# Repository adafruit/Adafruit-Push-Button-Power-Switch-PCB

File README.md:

## Adafruit Push Button Power Switch PCB
<a href="http://www.adafruit.com/products/1400"><br/>
Click here to purchase one from the Adafruit shop</a>

The Adafruit Push-button Power Switch is a tidy little design that lets you control a DC power source using an everyday tactile button. The breakout uses a latching analog circuit that is triggered by a push of the button. Press once to turn on, then press again to turn off. The circuit uses a 3A P-FET to connect and disconnect the IN pin to the OUT pin. Works great from 3V to 14VDC and up to 3A (although the FET gets a little toasty at continuous 3A draw) yet has only 0.5uA quiescent current draw.

Using it is easy: connect the power source to Ground and IN, then the load from Ground to OUT. We include a 12mm tactile switch that works well but you can solder in your own switch as well. Press the button (or short the button pins) to alternate between on or off. A on-board red LED will light up when active so you know its working. There's a fourth KILL pin, which you can use to turn off the load and/or keep it off even if the button is pressed. When 1 or more volts is applied it will instantly turn off the FET. This allows your project to turn itself off.

Comes with a assembled & tested bread-board friendly breakout board with four mounting holes, a 12mm tactile button, and some 0.1" male header you can solder to the board to plug it into a breadboard.

PCB files for the Push Button Power Switch PCB. The format is EagleCAD schematic and board layout
- https://www.adafruit.com/products/1400

### License

Adafruit invests time and resources providing this open source design, please support Adafruit and open-source hardware by purchasing products from [Adafruit](https://www.adafruit.com)!

All text above must be included in any redistribution

Designed by Limor Fried/Ladyada for Adafruit Industries.
Creative Commons Attribution/Share-Alike, all text above must be included in any redistribution. 
See license.txt for additional information.

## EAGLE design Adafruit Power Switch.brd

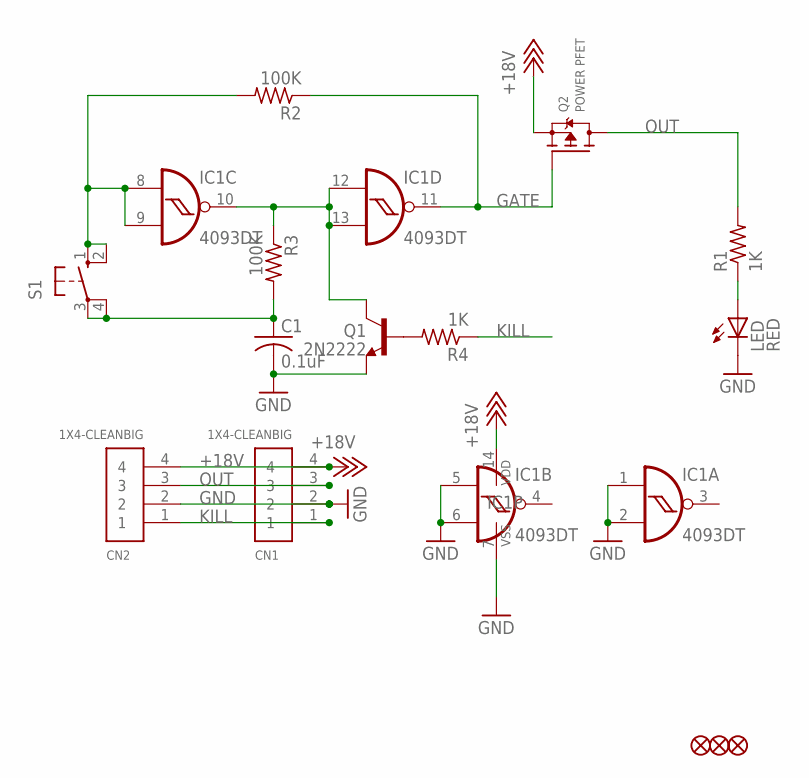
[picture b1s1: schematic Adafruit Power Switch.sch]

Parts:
C1: 0.1uF; C0805
CN1, CN2: 1X4-CLEANBIG; 1X04-CLEANBIG
FID1, FID2, FID3: FIDUCIAL""; FIDUCIAL_1MM
IC1: 4093DT; MC14093B-TSSOP14
LED: RED; CHIP-LED0805
Q1: 2N2222; SOT23-BEC
Q2: POWER PFET; SOT23-WIDE
R1, R4: 1K; R0805
R2, R3: 100K; R0805
S1: 40-XX-ROUND; B3F-40XX-ROUND

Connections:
+18V: CN1.4, CN2.4, IC1.14 (VDD), Q2.2 (S)
GATE: IC1.11 (O), Q2.1 (G), R2.1
GND: C1.2, CN1.2, CN2.2, IC1.1 (I0), IC1.2 (I1), IC1.5 (I0), IC1.6 (I1), IC1.7 (VSS), LED.C, Q1.E
KILL: CN1.1, CN2.1, R4.1
unnamed: Q1.B, R4.2
unnamed: IC1.10 (O), IC1.12 (I0), IC1.13 (I1), Q1.C, R3.1
unnamed: LED.A, R1.1
unnamed: C1.1, R3.2, S1.3, S1.4 (P1)
unnamed: IC1.8 (I0), IC1.9 (I1), R2.2, S1.1 (S), S1.2 (S1)
OUT: CN1.3, CN2.3, Q2.3 (D), R1.2

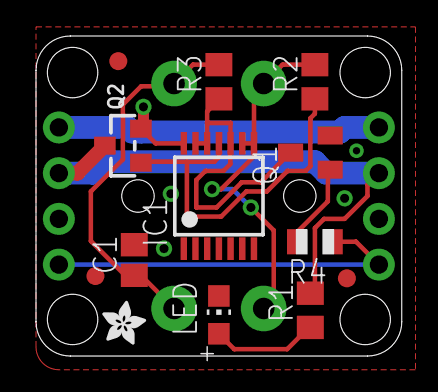
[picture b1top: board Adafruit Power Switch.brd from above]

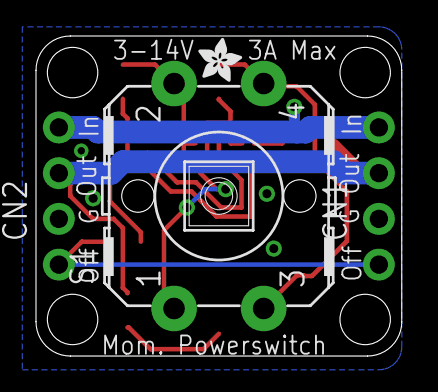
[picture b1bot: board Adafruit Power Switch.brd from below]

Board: 2 copper layers, 20.3 x 17.8 mm, 17 parts (4 on the bottom side), 10 nets.

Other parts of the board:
U$1, U$2: ADAFRUIT_2.5MM

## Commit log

2016-06-20 init-o-rama
2020-12-02 Correct trivial typo

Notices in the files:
parts and their libraries:
microbuilder: This work is placed in the public domain, and may be freely used for commercial and non-commercial work with the following conditions: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
